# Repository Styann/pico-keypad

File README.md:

# Anesidora

A 65% keyboard PCB for the Raspberry pi pico made with KiCad 8, and a custom firmware.

## Assembly

### THT components
- Raspberry Pico
- Keyboard Switches (x68)
- Keyboard Stabilizers
- Rotary Encoder
- Resistors 10KOhm (x4)
- Capacitors 0.1µF (x2)
- Diodes 1N4148 (x69)
- SSD1306 OLED display 128x32
- LEDs (x2)
- Resistors (x2 for LEDs)
- Button
- 2.54mm Male Pin Header 2x6

### SMD components
- leds WS2812B (x16)
- SMD Capacitors 0603 100nF (x16)

## 📦 Build the firmware
1.
Install the pico C/C++ SDK (https://www.raspberrypi.com/documentation/microcontrollers/c_sdk.html)

2.
```sh
export ANESIDORA_PATH=path/to/Anesidora
```

3.
```sh
export PICO_USB_DISK_PATH=path/to/RPI-RP2
```

4.
```sh
./deploy.sh --build --flash
```

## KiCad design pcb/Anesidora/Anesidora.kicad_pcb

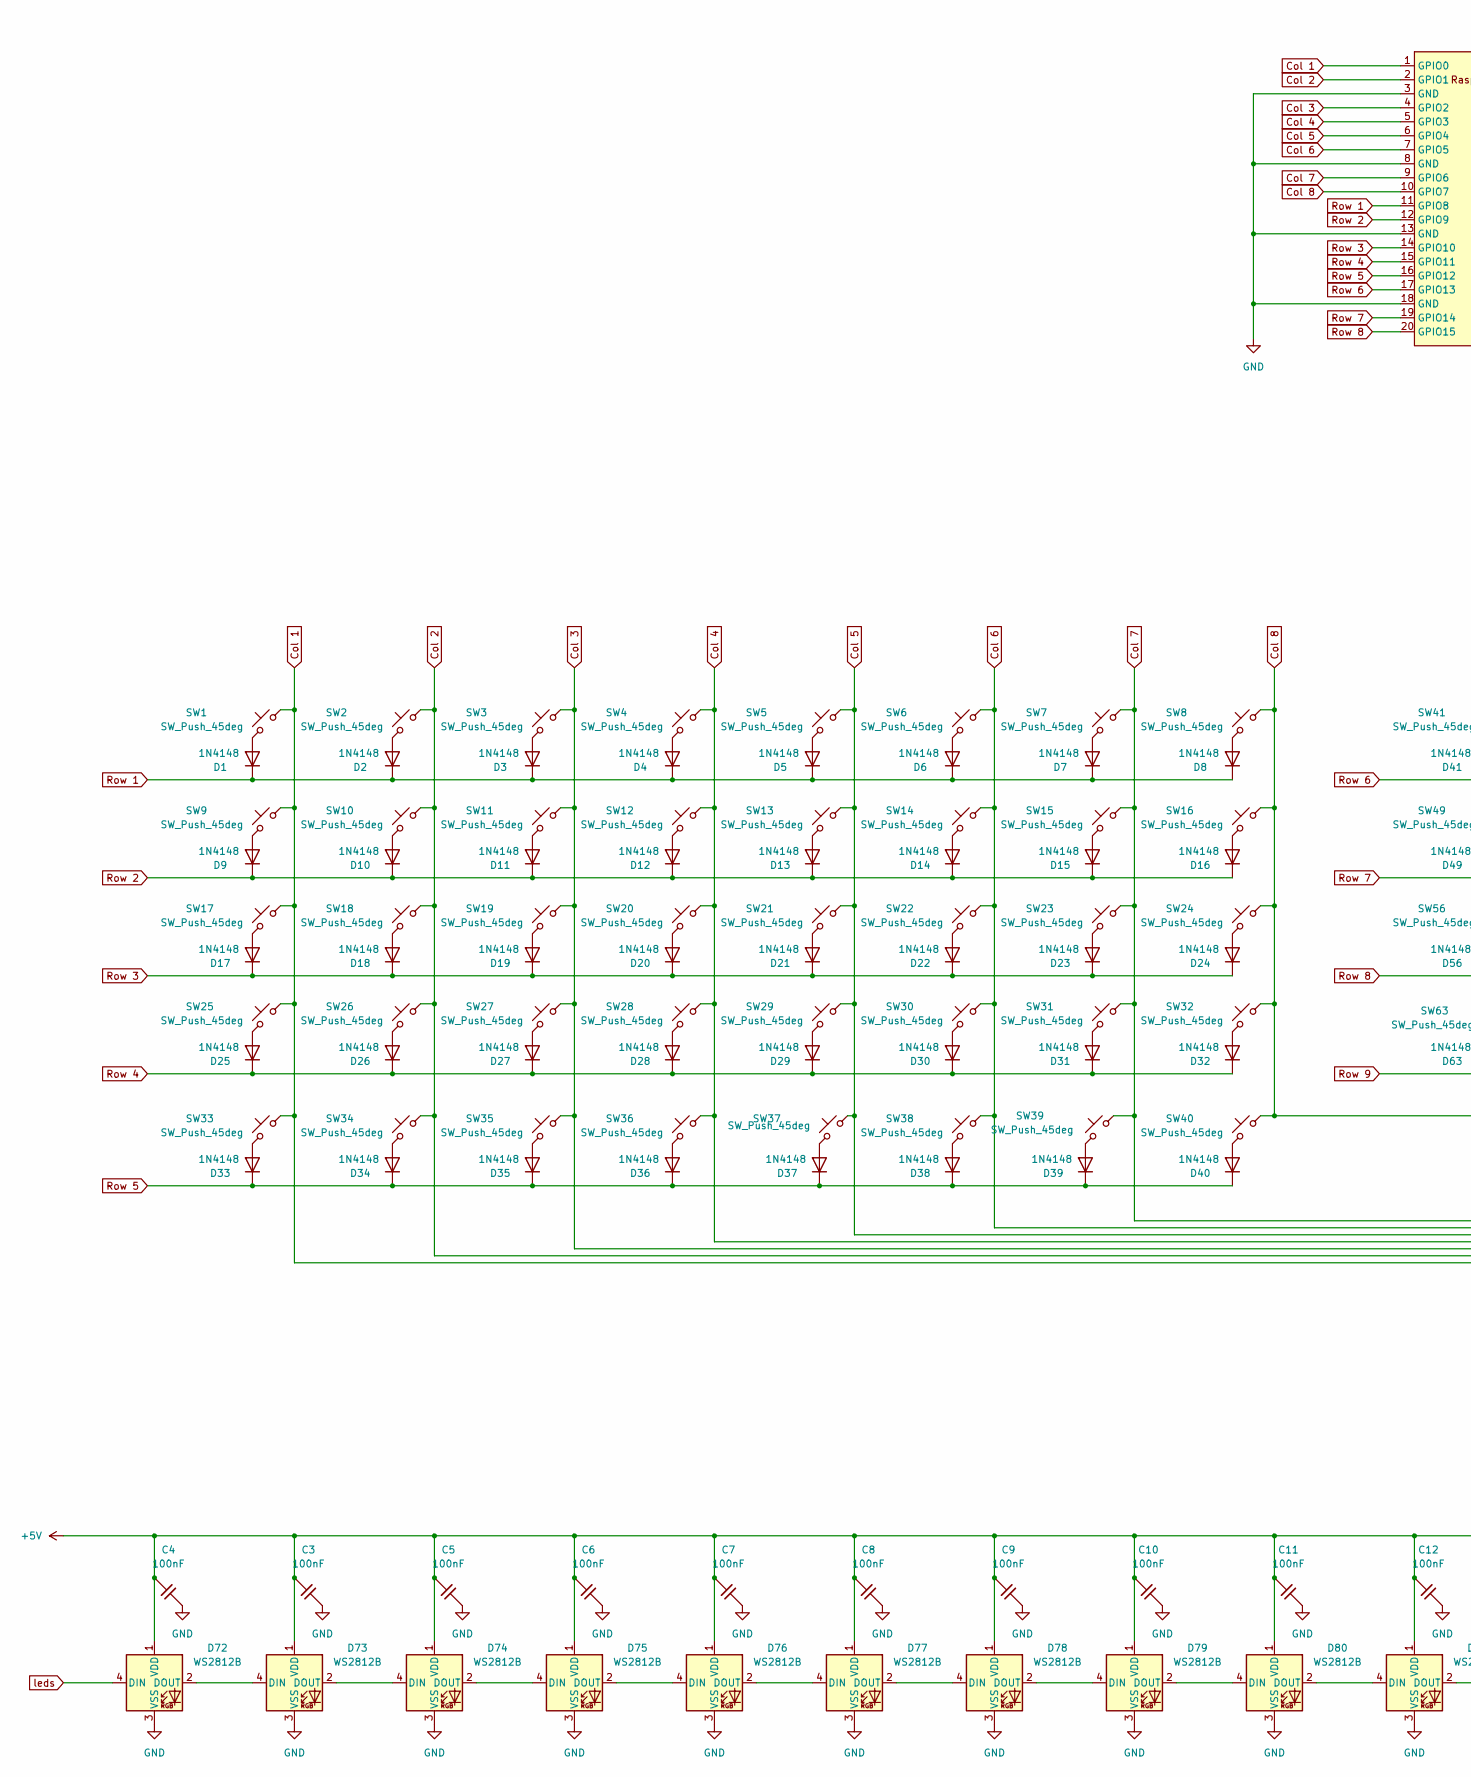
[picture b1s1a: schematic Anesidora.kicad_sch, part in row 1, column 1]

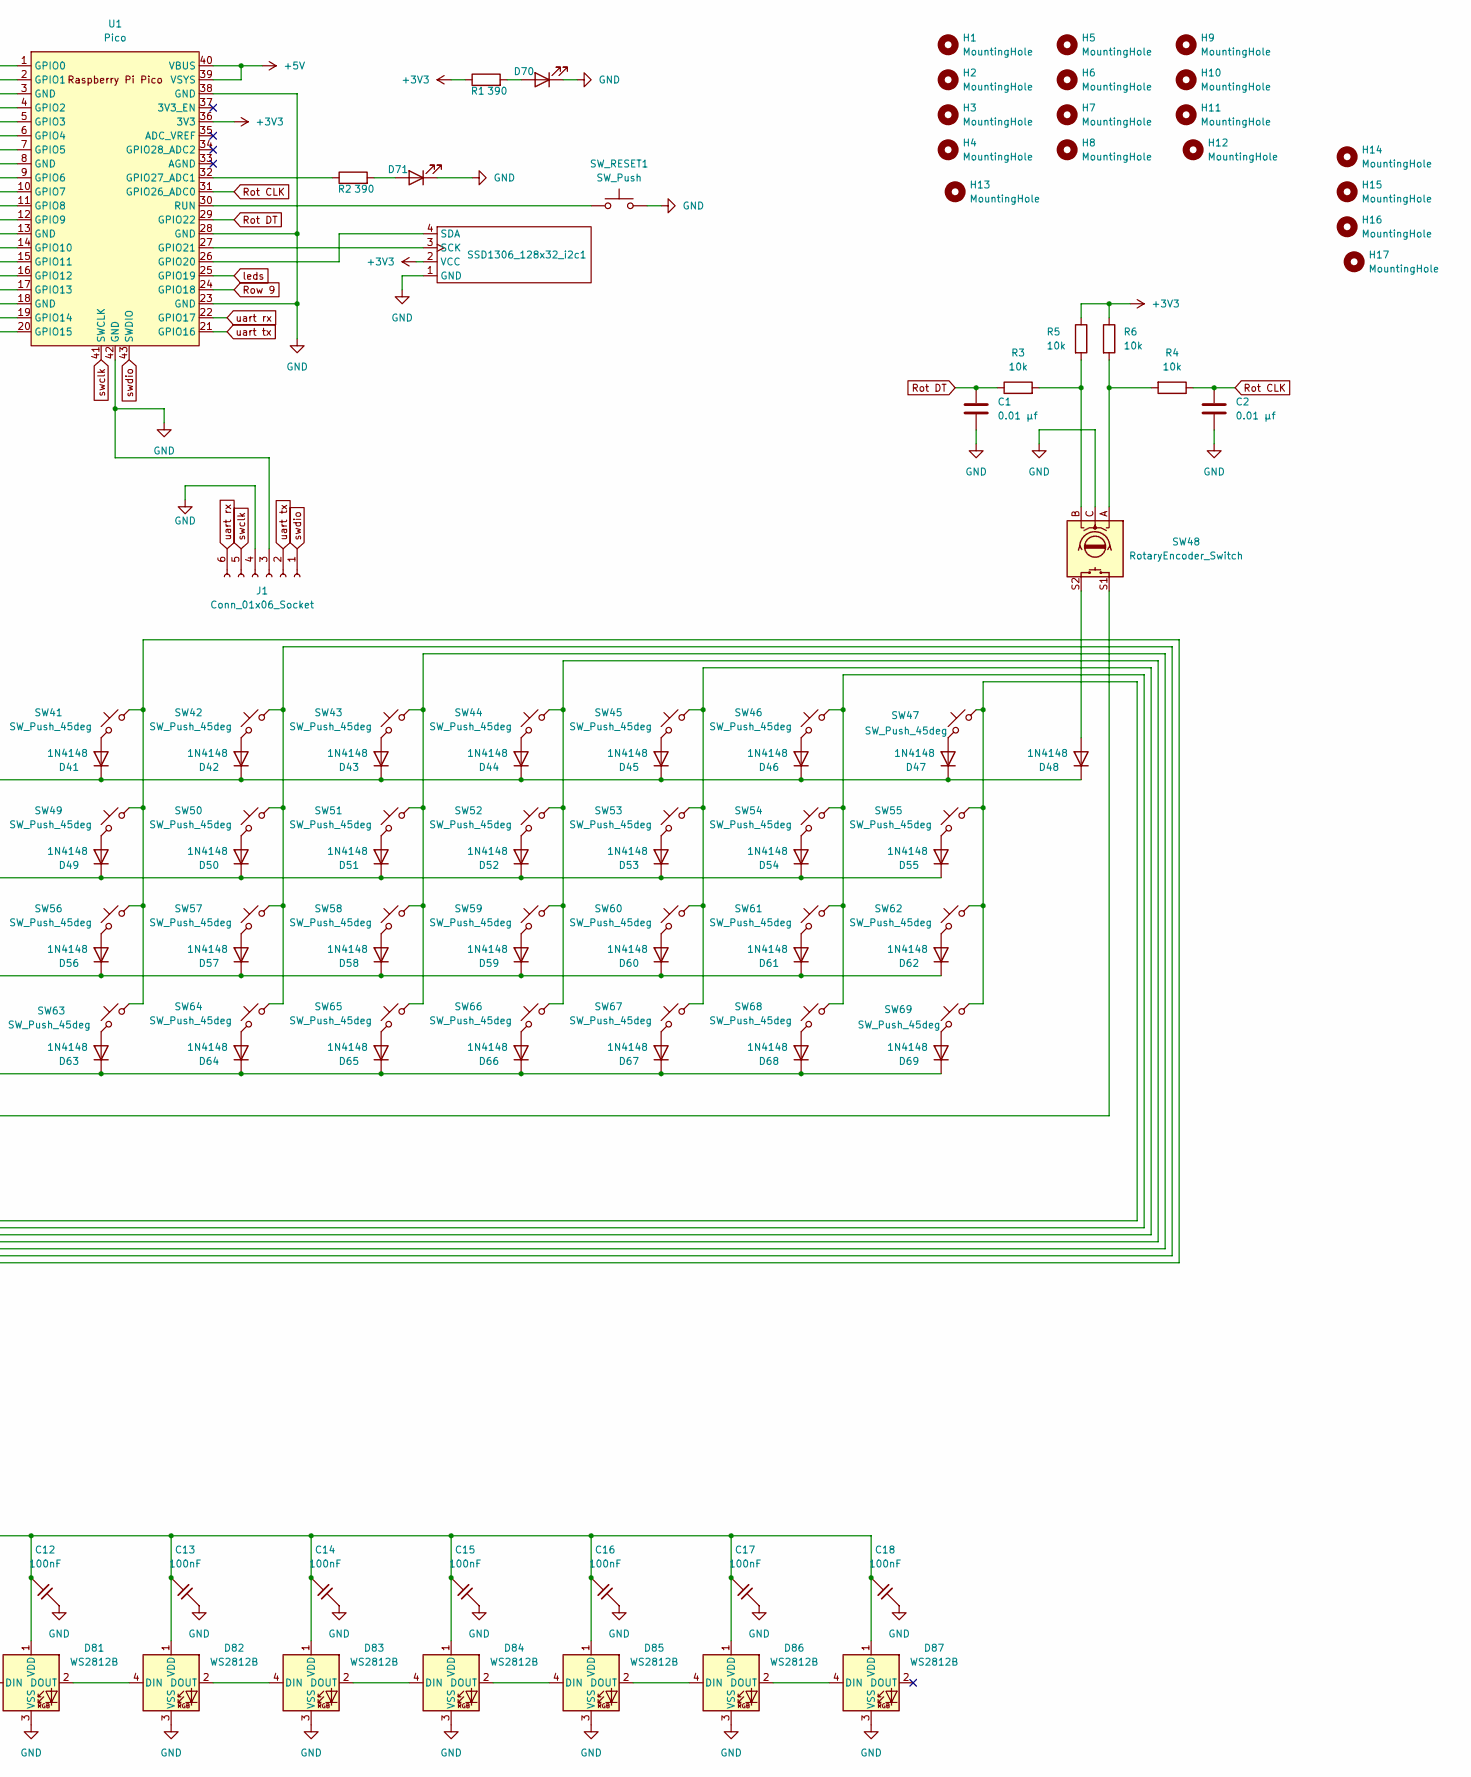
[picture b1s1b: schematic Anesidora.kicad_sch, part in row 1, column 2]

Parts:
C1, C2: 0.01 µf; C_Disc_D3.0mm_W1.6mm_P2.50mm
C3, C4, C5, C6, C7, C8, C9, C10, C11, C12, C13, C14, C15, C16, C17, C18: 100nF; C_0603_1608Metric
D1, D2, D3, D4, D5, D6, D7, D8, D9, D10, D11, D12, D13, D14, D15, D16, D17, D18, D19, D20, D21, D22, D23, D24, D25, D26, D27, D28, D29, D30, D31, D32, D33, D34, D35, D36, D37, D38, D39, D40, D41, D42, D43, D44, D45, D46, D47, D48, D49, D50, D51, D52, D53, D54, D55, D56, D57, D58, D59, D60, D61, D62, D63, D64, D65, D66, D67, D68, D69: 1N4148; D_DO-35_SOD27_P7.62mm_Horizontal
D70, D71: LED; LED_D5.0mm
D72, D73, D74, D75, D76, D77, D78, D79, D80, D81, D82, D83, D84, D85, D86, D87: WS2812B; LED_WS2812B_PLCC4_5.0x5.0mm_P3.2mm
H1, H2, H3, H4, H5, H6, H7, H8, H9, H10, H11, H12, H13, H14, H15, H16, H17: MountingHole; MountingHole_2.2mm_M2_Pad
J1: Conn_01x06_Socket; PinHeader_2x03_P2.54mm_Vertical
R1, R2: 390; R_Axial_DIN0207_L6.3mm_D2.5mm_P10.16mm_Horizontal
R3, R4, R5, R6: 10k; R_Axial_DIN0207_L6.3mm_D2.5mm_P10.16mm_Horizontal
SSD1306_128x32_i2c1: SSD1306_128x32_i2c
SW1, SW2, SW3, SW4, SW5, SW6, SW7, SW8, SW10, SW11, SW12, SW13, SW14, SW15, SW16, SW18, SW19, SW20, SW21, SW22, SW23, SW24, SW26, SW27, SW28, SW29, SW30, SW31, SW32, SW37, SW38, SW39, SW40, SW41, SW42, SW43, SW44, SW45, SW47, SW49, SW50, SW51, SW52, SW53, SW55, SW56, SW57, SW58, SW59, SW61, SW62, SW63, SW64, SW65, SW67, SW68, SW69: SW_Push_45deg; SW_Cherry_MX_PCB_1.00u
SW9, SW54: SW_Push_45deg; SW_Cherry_MX_PCB_1.50u
SW17, SW66: SW_Push_45deg; SW_Cherry_MX_PCB_1.75u
SW25, SW60: SW_Push_45deg; SW_Cherry_MX_PCB_2.25u
SW33, SW34, SW35: SW_Push_45deg; SW_Cherry_MX_PCB_1.25u
SW36: SW_Push_45deg; SW_Cherry_MX_PCB_6.25u
SW46: SW_Push_45deg; SW_Cherry_MX_PCB_2.00u
SW48: RotaryEncoder_Switch; RotaryEncoder_Alps_EC11E-Switch_Vertical_H20mm
SW_RESET1: SW_Push; SW_PUSH_6mm
U1: Pico; RPi_Pico_SMD_TH

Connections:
+3V3: R1.1, R5.1, R6.1, SSD1306_128x32_i2c1.2 (VCC), U1.36 (3V3); also elsewhere on the board
+5V: C3.2, C4.2, C5.2, C6.2, C7.2, C8.2, C9.2, C10.2, C11.2, C12.2, C13.2, C14.2, C15.2, C16.2, C17.2, C18.2, D72.1 (VDD), D73.1 (VDD), D74.1 (VDD), D75.1 (VDD), D76.1 (VDD), D77.1 (VDD), D78.1 (VDD), D79.1 (VDD), D80.1 (VDD), D81.1 (VDD), D82.1 (VDD), D83.1 (VDD), D84.1 (VDD), D85.1 (VDD), D86.1 (VDD), D87.1 (VDD), U1.39 (VSYS), U1.40 (VBUS); also elsewhere on the board
Col 1: SW1.2, SW9.2, SW17.2, SW25.2, SW33.2, SW41.2, SW49.2, SW56.2, SW63.2, U1.1 (GPIO0); also elsewhere on the board
Col 2: SW2.2, SW10.2, SW18.2, SW26.2, SW34.2, SW42.2, SW50.2, SW57.2, SW64.2, U1.2 (GPIO1); also elsewhere on the board
Col 3: SW3.2, SW11.2, SW19.2, SW27.2, SW35.2, SW43.2, SW51.2, SW58.2, SW65.2, U1.4 (GPIO2); also elsewhere on the board
Col 4: SW4.2, SW12.2, SW20.2, SW28.2, SW36.2, SW44.2, SW52.2, SW59.2, SW66.2, U1.5 (GPIO3); also elsewhere on the board
Col 5: SW5.2, SW13.2, SW21.2, SW29.2, SW37.2, SW45.2, SW53.2, SW60.2, SW67.2, U1.6 (GPIO4); also elsewhere on the board
Col 6: SW6.2, SW14.2, SW22.2, SW30.2, SW38.2, SW46.2, SW54.2, SW61.2, SW68.2, U1.7 (GPIO5); also elsewhere on the board
Col 7: SW7.2, SW15.2, SW23.2, SW31.2, SW39.2, SW47.2, SW55.2, SW62.2, SW69.2, U1.9 (GPIO6); also elsewhere on the board
Col 8: SW8.2, SW16.2, SW24.2, SW32.2, SW40.2, SW48.S1, U1.10 (GPIO7); also elsewhere on the board
GND: C1.2, C2.2, C3.1, C4.1, C5.1, C6.1, C7.1, C8.1, C9.1, C10.1, C11.1, C12.1, C13.1, C14.1, C15.1, C16.1, C17.1, C18.1, D70.1 (K), D71.1 (K), D72.3 (VSS), D73.3 (VSS), D74.3 (VSS), D75.3 (VSS), D76.3 (VSS), D77.3 (VSS), D78.3 (VSS), D79.3 (VSS), D80.3 (VSS), D81.3 (VSS), D82.3 (VSS), D83.3 (VSS), D84.3 (VSS), D85.3 (VSS), D86.3 (VSS), D87.3 (VSS), J1.3, J1.4, SSD1306_128x32_i2c1.1 (GND), SW48.C, SW_RESET1.2, U1.3 (GND), U1.8 (GND), U1.13 (GND), U1.18 (GND), U1.23 (GND), U1.28 (GND), U1.38 (GND), U1.42 (GND); also elsewhere on the board
unnamed: D1.2 (A), SW1.1
unnamed: D2.2 (A), SW2.1
unnamed: D3.2 (A), SW3.1
unnamed: D4.2 (A), SW4.1
unnamed: D5.2 (A), SW5.1
unnamed: D6.2 (A), SW6.1
unnamed: D7.2 (A), SW7.1
unnamed: D8.2 (A), SW8.1
unnamed: D9.2 (A), SW9.1
unnamed: D10.2 (A), SW10.1
unnamed: D11.2 (A), SW11.1
unnamed: D12.2 (A), SW12.1
unnamed: D13.2 (A), SW13.1
unnamed: D14.2 (A), SW14.1
unnamed: D15.2 (A), SW15.1
unnamed: D16.2 (A), SW16.1
unnamed: D17.2 (A), SW17.1
unnamed: D18.2 (A), SW18.1
unnamed: D19.2 (A), SW19.1
unnamed: D20.2 (A), SW20.1
unnamed: D21.2 (A), SW21.1
unnamed: D22.2 (A), SW22.1
unnamed: D23.2 (A), SW23.1
unnamed: D24.2 (A), SW24.1
unnamed: D25.2 (A), SW25.1
unnamed: D26.2 (A), SW26.1
unnamed: D27.2 (A), SW27.1
unnamed: D28.2 (A), SW28.1
unnamed: D29.2 (A), SW29.1
unnamed: D30.2 (A), SW30.1
unnamed: D31.2 (A), SW31.1
unnamed: D32.2 (A), SW32.1
unnamed: D33.2 (A), SW33.1
unnamed: D34.2 (A), SW34.1
unnamed: D35.2 (A), SW35.1
unnamed: D36.2 (A), SW36.1
unnamed: D37.2 (A), SW37.1
unnamed: D38.2 (A), SW38.1
unnamed: D39.2 (A), SW39.1
unnamed: D40.2 (A), SW40.1
unnamed: D41.2 (A), SW41.1
unnamed: D42.2 (A), SW42.1
unnamed: D43.2 (A), SW43.1
unnamed: D44.2 (A), SW44.1
unnamed: D45.2 (A), SW45.1
unnamed: D46.2 (A), SW46.1
unnamed: D47.2 (A), SW47.1
unnamed: D48.2 (A), SW48.S2
unnamed: D49.2 (A), SW49.1
unnamed: D50.2 (A), SW50.1
unnamed: D51.2 (A), SW51.1
unnamed: D52.2 (A), SW52.1
unnamed: D53.2 (A), SW53.1
unnamed: D54.2 (A), SW54.1
unnamed: D55.2 (A), SW55.1
unnamed: D56.2 (A), SW56.1
unnamed: D57.2 (A), SW57.1
unnamed: D58.2 (A), SW58.1
unnamed: D59.2 (A), SW59.1
unnamed: D60.2 (A), SW60.1
unnamed: D61.2 (A), SW61.1
unnamed: D62.2 (A), SW62.1
unnamed: D63.2 (A), SW63.1
unnamed: D64.2 (A), SW64.1
unnamed: D65.2 (A), SW65.1
unnamed: D66.2 (A), SW66.1
unnamed: D67.2 (A), SW67.1
unnamed: D68.2 (A), SW68.1
unnamed: D69.2 (A), SW69.1
unnamed: D70.2 (A), R1.2
unnamed: D71.2 (A), R2.2
unnamed: D72.2 (DOUT), D73.4 (DIN)
unnamed: D73.2 (DOUT), D74.4 (DIN)
unnamed: D74.2 (DOUT), D75.4 (DIN)
unnamed: D75.2 (DOUT), D76.4 (DIN)
unnamed: D76.2 (DOUT), D77.4 (DIN)
unnamed: D77.2 (DOUT), D78.4 (DIN)
unnamed: D78.2 (DOUT), D79.4 (DIN)
unnamed: D79.2 (DOUT), D80.4 (DIN)
unnamed: D80.2 (DOUT), D81.4 (DIN)
unnamed: D81.2 (DOUT), D82.4 (DIN)
unnamed: D82.2 (DOUT), D83.4 (DIN)
unnamed: D83.2 (DOUT), D84.4 (DIN)
unnamed: D84.2 (DOUT), D85.4 (DIN)
unnamed: D85.2 (DOUT), D86.4 (DIN)
unnamed: D86.2 (DOUT), D87.4 (DIN)
unnamed: R3.2, R5.2, SW48.B
unnamed: R4.2, R6.2, SW48.A
unnamed 99: SSD1306_128x32_i2c1.3 (SCK), U1.27 (GPIO21); also elsewhere on the board
unnamed 100: SSD1306_128x32_i2c1.4 (SDA), U1.26 (GPIO20); also elsewhere on the board
unnamed: SW_RESET1.1, U1.30 (RUN)
unnamed 102: R2.1, U1.32 (GPIO27_ADC1); also elsewhere on the board
Rot CLK: C2.1, R4.1, U1.31 (GPIO26_ADC0); also elsewhere on the board
Rot DT: C1.1, R3.1, U1.29 (GPIO22); also elsewhere on the board
Row 1: D1.1 (K), D2.1 (K), D3.1 (K), D4.1 (K), D5.1 (K), D6.1 (K), D7.1 (K), D8.1 (K), U1.11 (GPIO8); also elsewhere on the board
Row 2: D9.1 (K), D10.1 (K), D11.1 (K), D12.1 (K), D13.1 (K), D14.1 (K), D15.1 (K), D16.1 (K), U1.12 (GPIO9); also elsewhere on the board
Row 3: D17.1 (K), D18.1 (K), D19.1 (K), D20.1 (K), D21.1 (K), D22.1 (K), D23.1 (K), D24.1 (K), U1.14 (GPIO10); also elsewhere on the board
Row 4: D25.1 (K), D26.1 (K), D27.1 (K), D28.1 (K), D29.1 (K), D30.1 (K), D31.1 (K), D32.1 (K), U1.15 (GPIO11); also elsewhere on the board
Row 5: D33.1 (K), D34.1 (K), D35.1 (K), D36.1 (K), D37.1 (K), D38.1 (K), D39.1 (K), D40.1 (K), U1.16 (GPIO12); also elsewhere on the board
Row 6: D41.1 (K), D42.1 (K), D43.1 (K), D44.1 (K), D45.1 (K), D46.1 (K), D47.1 (K), D48.1 (K), U1.17 (GPIO13); also elsewhere on the board
Row 7: D49.1 (K), D50.1 (K), D51.1 (K), D52.1 (K), D53.1 (K), D54.1 (K), D55.1 (K), U1.19 (GPIO14); also elsewhere on the board
Row 8: D56.1 (K), D57.1 (K), D58.1 (K), D59.1 (K), D60.1 (K), D61.1 (K), D62.1 (K), U1.20 (GPIO15); also elsewhere on the board
Row 9: D63.1 (K), D64.1 (K), D65.1 (K), D66.1 (K), D67.1 (K), D68.1 (K), D69.1 (K), U1.24 (GPIO18); also elsewhere on the board
leds: D72.4 (DIN), U1.25 (GPIO19); also elsewhere on the board
swclk: J1.5, U1.41 (SWCLK); also elsewhere on the board
swdio: J1.1, U1.43 (SWDIO); also elsewhere on the board
uart rx: J1.6, U1.22 (GPIO17); also elsewhere on the board
uart tx: J1.2, U1.21 (GPIO16); also elsewhere on the board

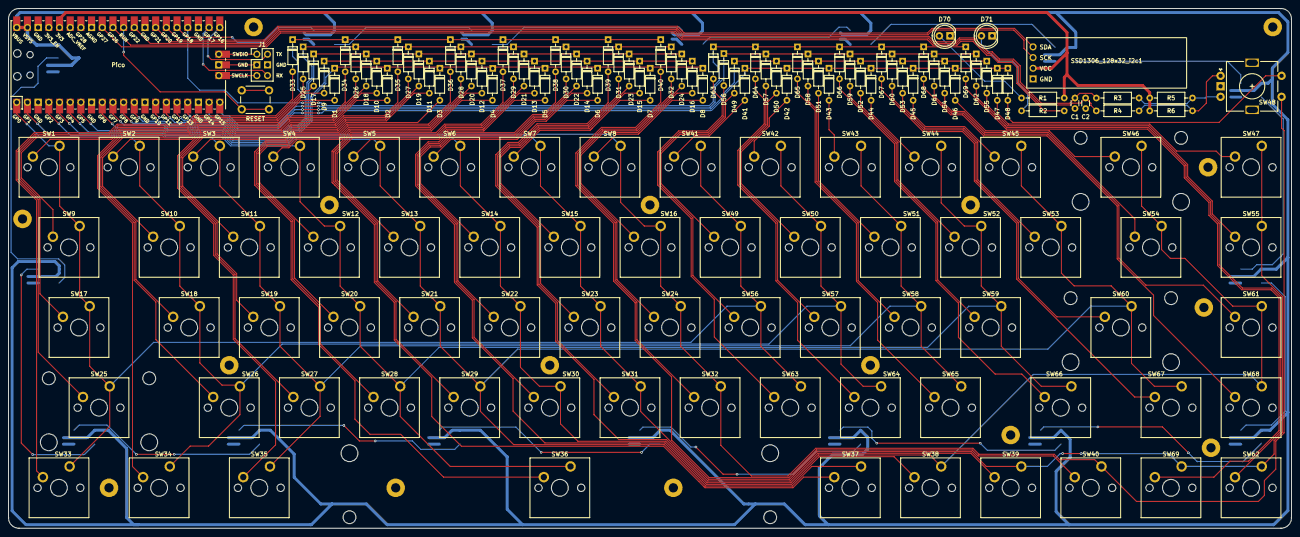
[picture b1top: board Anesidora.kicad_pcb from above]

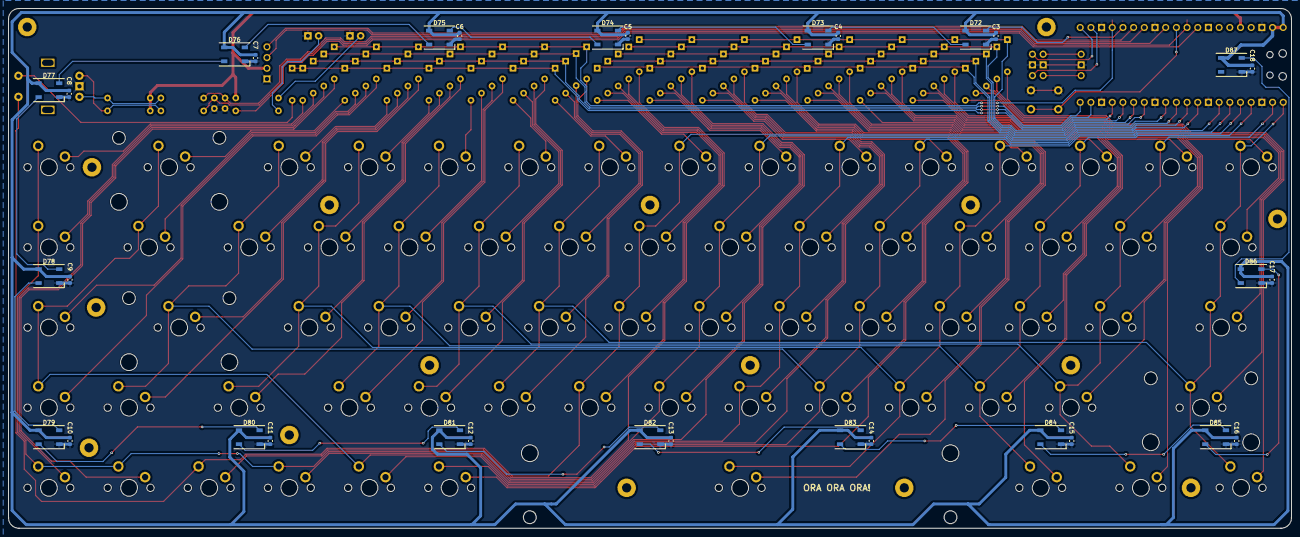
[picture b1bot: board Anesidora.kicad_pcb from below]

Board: 2 copper layers, 305.0 x 123.5 mm, 200 parts (32 on the bottom side), 119 nets.

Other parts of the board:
Pico: Pico; RPi_Pico_SMD_TH
RESET: SW_Push; SW_PUSH_6mm

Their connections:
+3V3: Pico.36 (3V3); also elsewhere on the board
+5V: Pico.39 (VSYS), Pico.40 (VBUS); also elsewhere on the board
Col 1: Pico.1 (GPIO0); also elsewhere on the board
Col 2: Pico.2 (GPIO1); also elsewhere on the board
Col 3: Pico.4 (GPIO2); also elsewhere on the board
Col 4: Pico.5 (GPIO3); also elsewhere on the board
Col 5: Pico.6 (GPIO4); also elsewhere on the board
Col 6: Pico.7 (GPIO5); also elsewhere on the board
Col 7: Pico.9 (GPIO6); also elsewhere on the board
Col 8: Pico.10 (GPIO7); also elsewhere on the board
GND: Pico.3 (GND), Pico.8 (GND), Pico.13 (GND), Pico.18 (GND), Pico.23 (GND), Pico.28 (GND), Pico.38 (GND), Pico.42 (GND), RESET.2; also elsewhere on the board
unnamed 99: Pico.27 (GPIO21); also elsewhere on the board
unnamed 100: Pico.26 (GPIO20); also elsewhere on the board
unnamed 102: Pico.32 (GPIO27_ADC1); also elsewhere on the board
unnamed: Pico.30 (RUN), RESET.1
Rot CLK: Pico.31 (GPIO26_ADC0); also elsewhere on the board
Rot DT: Pico.29 (GPIO22); also elsewhere on the board
Row 1: Pico.11 (GPIO8); also elsewhere on the board
Row 2: Pico.12 (GPIO9); also elsewhere on the board
Row 3: Pico.14 (GPIO10); also elsewhere on the board
Row 4: Pico.15 (GPIO11); also elsewhere on the board
Row 5: Pico.16 (GPIO12); also elsewhere on the board
Row 6: Pico.17 (GPIO13); also elsewhere on the board
Row 7: Pico.19 (GPIO14); also elsewhere on the board
Row 8: Pico.20 (GPIO15); also elsewhere on the board
Row 9: Pico.24 (GPIO18); also elsewhere on the board
leds: Pico.25 (GPIO19); also elsewhere on the board
swclk: Pico.41 (SWCLK); also elsewhere on the board
swdio: Pico.43 (SWDIO); also elsewhere on the board
uart rx: Pico.22 (GPIO17); also elsewhere on the board
uart tx: Pico.21 (GPIO16); also elsewhere on the board

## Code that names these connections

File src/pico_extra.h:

#ifndef PICO_EXTRA_H
#define PICO_EXTRA_H

#include "pico/stdlib.h"
#include "hardware/spi.h"

#define LOW 0
#define HIGH 1

#define GPIO_IRQ_CHANGE (GPIO_IRQ_EDGE_FALL | GPIO_IRQ_EDGE_RISE)

#define BIT_SIZE_OF(type) (sizeof(type) * 8)

enum GPIO {
    GPIO0 = 0,
    GPIO1,
    GPIO2,
    GPIO3,
    GPIO4,
    GPIO5,
    GPIO6,
    GPIO7,
    GPIO8,
    GPIO9,
    GPIO10,
    GPIO11,
    GPIO12,
    GPIO13,
    GPIO14,
    GPIO15,
    GPIO16,
    GPIO17,
    GPIO18,
    GPIO19,
    GPIO20,
    GPIO21,
    GPIO22,
    GPIO25 = 25,
    GPIO26 = 26,
    GPIO27 = 27,
    GPIO28 = 28,
};

static inline uint32_t millis(void) {
    return to_ms_since_boot(get_absolute_time());
}

static inline void built_in_led_init(void) {
    gpio_init(PICO_DEFAULT_LED_PIN);
    gpio_set_dir(PICO_DEFAULT_LED_PIN, GPIO_OUT);
}

static inline void built_in_led_on(void) {
    gpio_put(PICO_DEFAULT_LED_PIN, HIGH);
}

static inline void built_in_led_off(void) {
    gpio_put(PICO_DEFAULT_LED_PIN, LOW);
}

static inline void built_in_led_put(bool value) {
    gpio_put(PICO_DEFAULT_LED_PIN, value);
}

/**
 * @brief select a spi device
 * @param pin_cs
 */
static inline void spi_chip_select(uint8_t pin_cs) {
    asm volatile("nop \n nop \n nop");
    gpio_put(pin_cs, LOW);
    asm volatile("nop \n nop \n nop");
}

/**
 * @brief deselect a spi device
 * @param pin_cs
 */
static inline void spi_chip_deselect(uint8_t pin_cs) {
    asm volatile("nop \n nop \n nop");
    gpio_put(pin_cs, HIGH);
    asm volatile("nop \n nop \n nop");
}

static inline void spi_set_format_from_inst(spi_inst_t *spi, uint data_bits) {
    spi_cpol_t cpol = (spi == spi0) ? SPI_CPOL_0 : SPI_CPOL_1;
    spi_cpha_t cpha = (spi == spi0) ? SPI_CPHA_0 : SPI_CPHA_1;
    spi_set_format(spi, data_bits, cpol,  cpha, SPI_MSB_FIRST);
}

static inline void spi_set_format_8(spi_inst_t *spi) {
    spi_set_format_from_inst(spi, 8);
}

static inline void spi_set_format_16(spi_inst_t *spi) {
    spi_set_format_from_inst(spi, 16);
}

#endif

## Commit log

2023-11-16 test
2023-11-16 Revert "idk"
    This reverts commit bf70b21e7fe9587d78e260829be40ddc311c9e97.
2023-11-17 started to add first layout
2023-11-20 add volume key
2023-12-10 rename repo, add busy wait
2023-12-10 add function to scan a row and one key, add description in README.md, modify path in CMakeLists
2023-12-13 add .gitignore, started to code multi modifiers keys.
2023-12-13 Update .gitignore
    update gitignore
2023-12-17 handling multiple keypress, remade layout with custom typedef
2023-12-28 remove unused lines in CMakeList.txt, rename struct key_t to keyboard_key_t, now using loop to scan keyboard's keys
2024-01-07 starting to write my own usb driver
2024-01-14 update CMakeLists, add hid descriptor and hid interface
2024-01-14 add HID REPORT and SET_IDLE request handling, add led for debugging
2024-01-16 add prototypes, create usb_hid.h, rename Keys to keys
2024-01-16 add sending hid keyboard report from device to host, and some little fix
2024-01-20 sending keyboard report work on linux
2024-01-21 add diagram, optimize keys matrix scanning,
2024-02-05 add is_key_pressed and is_keyboard_report_empty function, add toggle switch, add great packet transfer (bigger than the buffer size) , start consumer control handling.
2024-02-08 add comment, done great_packet_transfer
2024-02-11 add possibility to make shortcut, break scan matrix loop when report is full, fix ghosting, delete keyboard_key_t
2024-02-21 add rgb led strip, update README, remove hid task timer
2024-03-03 remove timer, add consumer control in keyboard report, add leds in usb_hid
2024-04-01 add rotary encode, leds indicator, rgb leds
2024-04-03 rotary encoder using interrutps, remove led_indicator directories
2024-04-09 remake circuit diagram, add hw040 and ws2812b drivers
2024-04-14 leds works, rename long name with this
2024-04-29 +fix report spamming, add conditional preprocessor
2024-05-01 remove rgb_led_strip, rename some things, add gamepad report
2024-05-09 + joystick and button api, arcade stick report descriptor and more
2024-06-05 + ssd1331 driver, weak set_report_callback, some refactoring and fixes
2024-06-15 + macro handling, improve ws2812b driver
2024-06-25 + rename and move some files, some fixes and fix great usb xfer
2024-06-25 + add kicad sch and pcb
2024-06-27 + update pcb
2024-07-01 + update sch and pcb
2024-07-04 + blaziken animation
2024-08-03 + update pcb and schematic (add led)
2024-08-04 + update ssd1331 footprint
2024-08-18 + ssd1331 text, refactor usb, changed hw040 to rotary encoder...
2024-08-24 + some changes
2024-09-07 update pcb (remove one led and ssd1331 spi)
2024-09-08 adding somes macros
2024-09-17 + rename this to self, graphics font editor, many changes
2024-10-18 + refactoring, start usb mice support, rm macro, st7735s driver
2024-10-21 + update pcb (redo all the layout)
2024-10-22 + update pcb (swap right tracks layer)
2024-10-23 + update pcb, usb C hack
2024-10-28 + update pcb (qwerty layout)
2024-10-29 update pcb
2024-12-11 + some refactoring and update
2024-12-18 pcb v1
2024-12-19 little pcb fix
2024-12-27 firmware v1
2024-12-27 fix ground plane, update serigraphie
2024-12-28 pcb update
2024-12-28 add easter egg
2025-01-02 Create LICENSE
2025-01-03 + bongocat animation, ssd1306 & ws2812b deinit, start refactoring usb
2025-01-05 + usb refactoring - old oled display animations
2025-01-06 fix device descriptor wLength problem, fix config_descriptor wTotalLength
2025-01-11 fix ssd1306 pads size
2025-01-11 fix ssd1306 gnd pad size
2025-01-11 fix keyboard matrix busy wait and matrix key
2025-01-19 update README, deploy.sh, add macro to change leds color
2025-01-19 rename project
2025-01-19 change license
2025-01-19 rename kicad project
2025-01-28 fix spacebar size
2025-01-31 add mounting holes
